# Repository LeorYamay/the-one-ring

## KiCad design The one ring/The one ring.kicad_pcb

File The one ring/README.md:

# The One Ring — Hardware

KiCad PCB design for the *One Ring* wearable camera + speaker device.

## Contents
- `The one ring.kicad_sch` — schematic
- `The one ring.kicad_pcb` — PCB layout
- `The one ring.kicad_pro` — KiCad project file
- `fp-lib-table` — footprint library table
- `custom.pretty/` — custom footprints (including Adafruit MAX98357A breakout)

## Key components
| Ref | Part | Function |
|-----|------|----------|
| U1  | XIAO-ESP32-S3-Sense | MCU + camera + **onboard PDM mic** + WiFi/BLE |
| U2  | MAX98357A | I2S 3.2 W mono Class-D audio amp |
| SP1 | 8 ohm speaker | Audio output |
| SW1 | Tactile push button | User input |
| J1  | 1×2 pin header | Battery / power input |

## I2S audio wiring
| Signal | XIAO pin | MAX98357A pin |
|--------|----------|---------------|
| BCLK   | GPIO1 / D0 | BCLK (16) |
| LRCLK  | GPIO2 / D1 | LRCLK (14) |
| DIN    | GPIO3 / D2 | DIN (1) |
| SD     | GPIO4 / D3 | ~SD_MODE (4) |

Power rails: +3.3 V and +BATT (Li-Po via XIAO onboard JST).

## Onboard PDM microphone
The XIAO ESP32S3 Sense module has an **integrated PDM mic** (MSM261S4030H0R). Its pins are NOT exposed on the DIP header — they are internal module connections:

| Signal  | GPIO | Notes |
|---------|------|-------|
| PDM_CLK | 41   | Internal to module |
| PDM_DIN | 42   | Internal to module |

> ⚠️ **Firmware constraint:** On ESP32S3, PDM RX is **only supported on I2S0**. If your firmware assigns the PDM mic to `I2S_NUM_1` or `I2S_NUM_AUTO`, the device will crash into a boot loop. The speaker (standard I2S TX) should use `I2S_NUM_1`.

## Notes
- Connect +BATT to the XIAO onboard JST connector (not routed to the DIP header).
- Gain pin on MAX98357A is left floating for 9 dB default gain; tie to GND for 6 dB or VIN for 12 dB / 15 dB if needed.
- Speaker pads are top-left on the Adafruit breakout footprint; 7-pin signal header is bottom.

## Companion project
The matching PlatformIO firmware lives in the sibling repo/directory:
`~/projects/the one ring/` (note the space in the name).

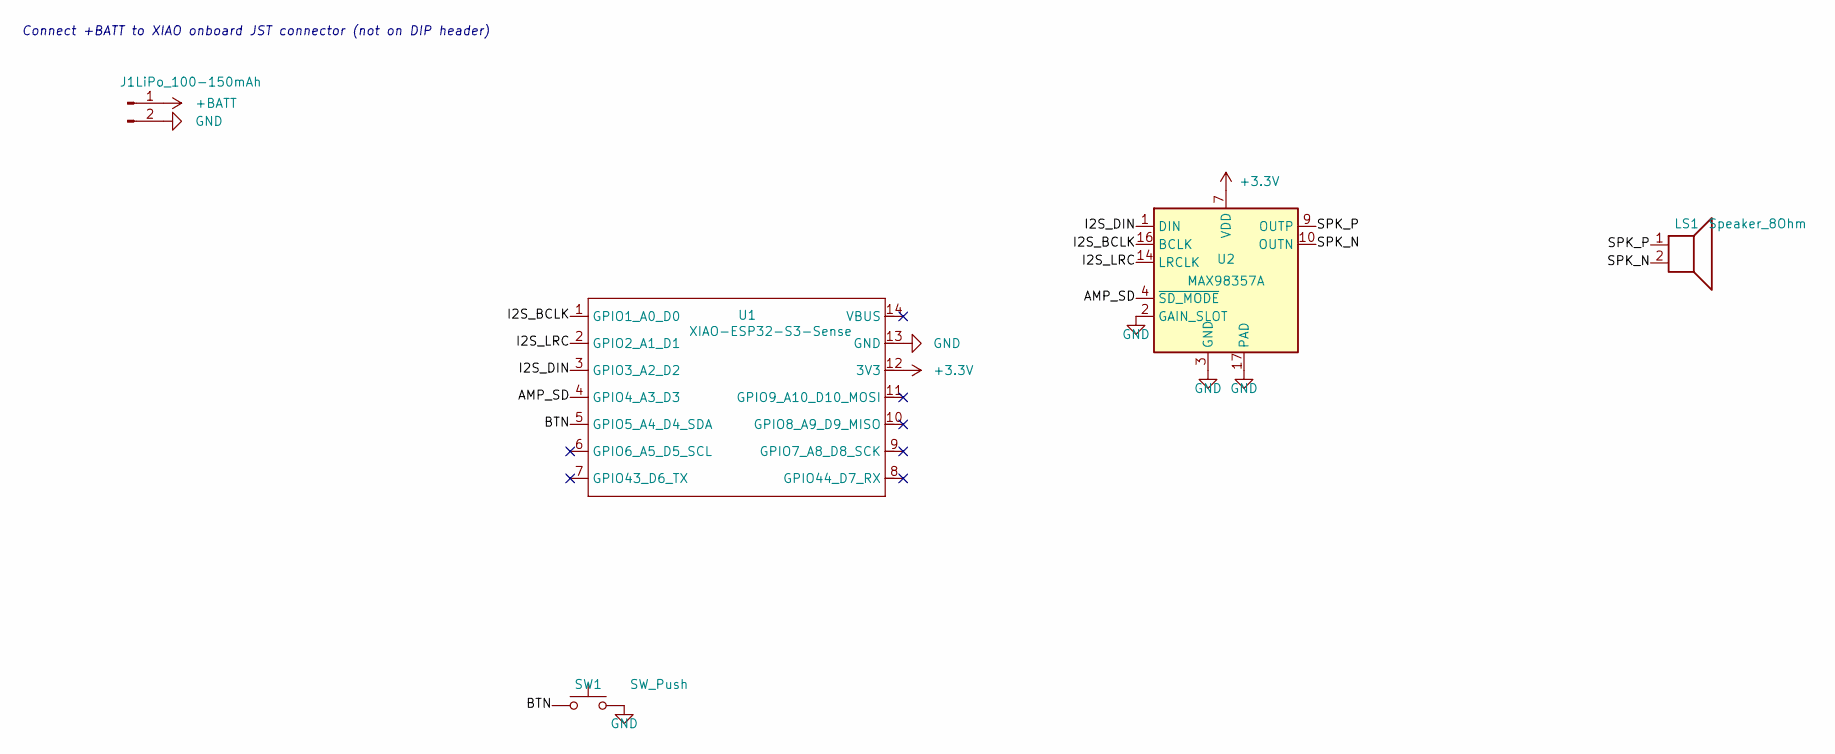
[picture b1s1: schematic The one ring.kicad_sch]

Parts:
J1: LiPo_100-150mAh; JST_PH_B2B-PH-K_1x02_P2.00mm_Vertical
LS1: Speaker_8Ohm; PinHeader_1x02_P2.54mm_Vertical
SW1: SW_Push; SW_PUSH_6mm
U1: XIAO-ESP32-S3-Sense; XIAO-ESP32-S3-DIP
U2: MAX98357A; Adafruit_MAX98357A_Breakout

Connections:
+3.3V: U1.12 (3V3), U2.7 (VDD), U2.8 (VDD)
+BATT: J1.1
/AMP_SD: U1.4 (GPIO4_A3_D3), U2.4 (~SD_MODE)
/BTN: SW1.1, U1.5 (GPIO5_A4_D4_SDA)
/I2S_BCLK: U1.1 (GPIO1_A0_D0), U2.16 (BCLK)
/I2S_DIN: U1.3 (GPIO3_A2_D2), U2.1 (DIN)
/I2S_LRC: U1.2 (GPIO2_A1_D1), U2.14 (LRCLK)
/SPK_N: LS1.2, U2.10 (OUTN)
/SPK_P: LS1.1, U2.9 (OUTP)
GND: J1.2, SW1.2, U1.13 (GND), U2.2 (GAIN_SLOT), U2.3 (GND), U2.11 (GND), U2.15 (GND), U2.17 (PAD)

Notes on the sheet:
Connect +BATT to XIAO onboard JST connector (not on DIP header)

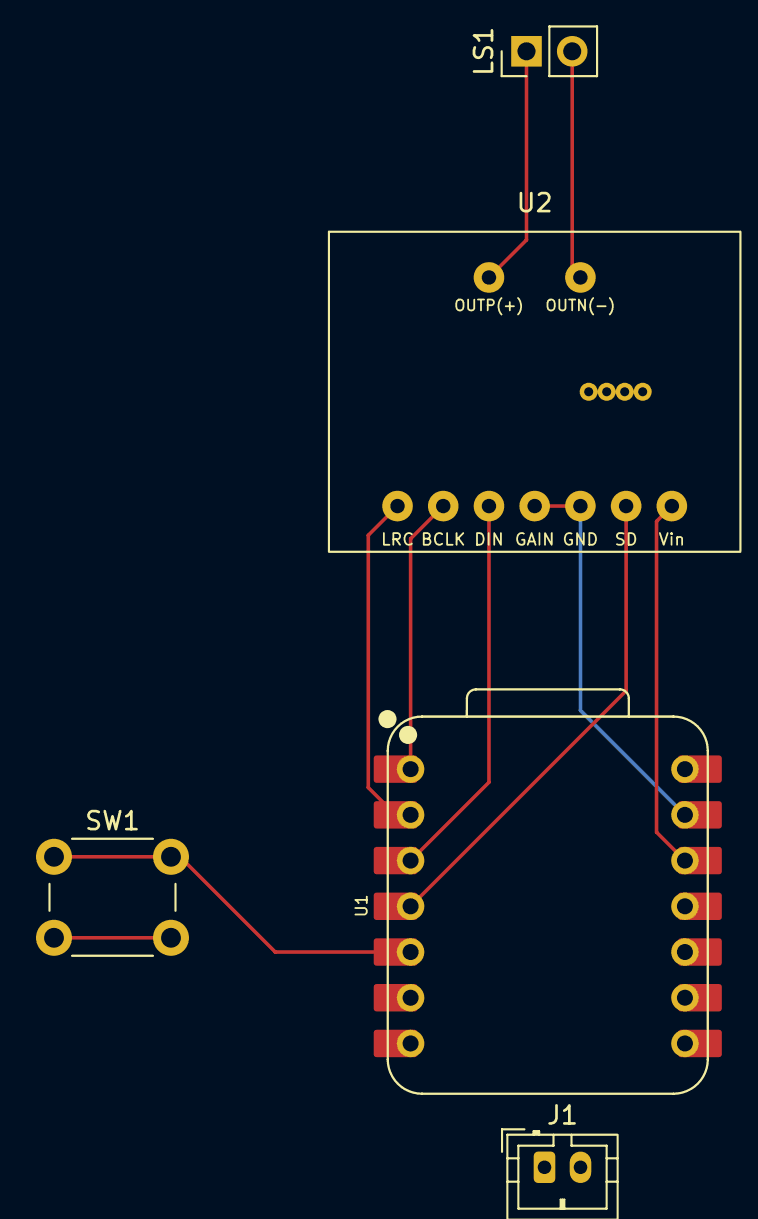
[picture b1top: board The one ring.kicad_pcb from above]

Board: 2 copper layers, 5 parts (0 on the bottom side), 9 nets.

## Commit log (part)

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2026-06-14 developer: add README with I2S0-PDM constraint note for hardware project
